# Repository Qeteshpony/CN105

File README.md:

# Mitsubishi CN105 compatible heatpump controller for ESPHome and Home Assistant

[Hardware Documentation](https://qeteshpony.github.io/CN105)

## Hardware fabrication

I ordered these boards from JLCPCB (Not a sponsor) and had only the smd components on the top side assembled. You then still need an ESP32-C6-WROOM-1 module (gets soldered on the bottom) and a Gaptec LME78_03-1.0 DC/DC Regulator. Also some header pins and a cable with a JST PAP-V-S PA 2.0 5 pin connector which goes into the CN105 port on the heatpumps main board. 

### Some details about the hardware

I decided to use the DC/DC regulator and pull power from the 12V pin of the heatpump since the 5V pin can't handle much current and I didn't want to risk damaging the heatpump. The 5V pin is just used for the pullups on the logic level converter since the heatpumps CN105 connector uses 5V logic which the ESP can't handle properly. 

LEDs 1 and 2 are connected to GPIO 23 and 22 and can be used freely by your software. 

LEDs 3 and 4 show activity on TX and RX and can be left out if you don't want the module to blink all the time... 

## Software

Mine are running with ESPHome and the external component found at [github.com/echavet/MitsubishiCN105ESPHome](https://github.com/echavet/MitsubishiCN105ESPHome)

Since this board uses the ESP32-C6, it can use WiFi as well as Thread to communicate with Home Assistant. 

Keep in mind that cheap serial adapters might not deliver enough power to successfully flash the ESP. I had to feed external power while flashing it. In that case only connect GND, RX and TX of the UART0 header to your serial adapter and feed anything between 6 and 36 volts (That's what the LME78 can handle) into the 12V pin of the boards CN105 header. 
When using ESPHome this is also just needed once. Updates can then be installed OTA.

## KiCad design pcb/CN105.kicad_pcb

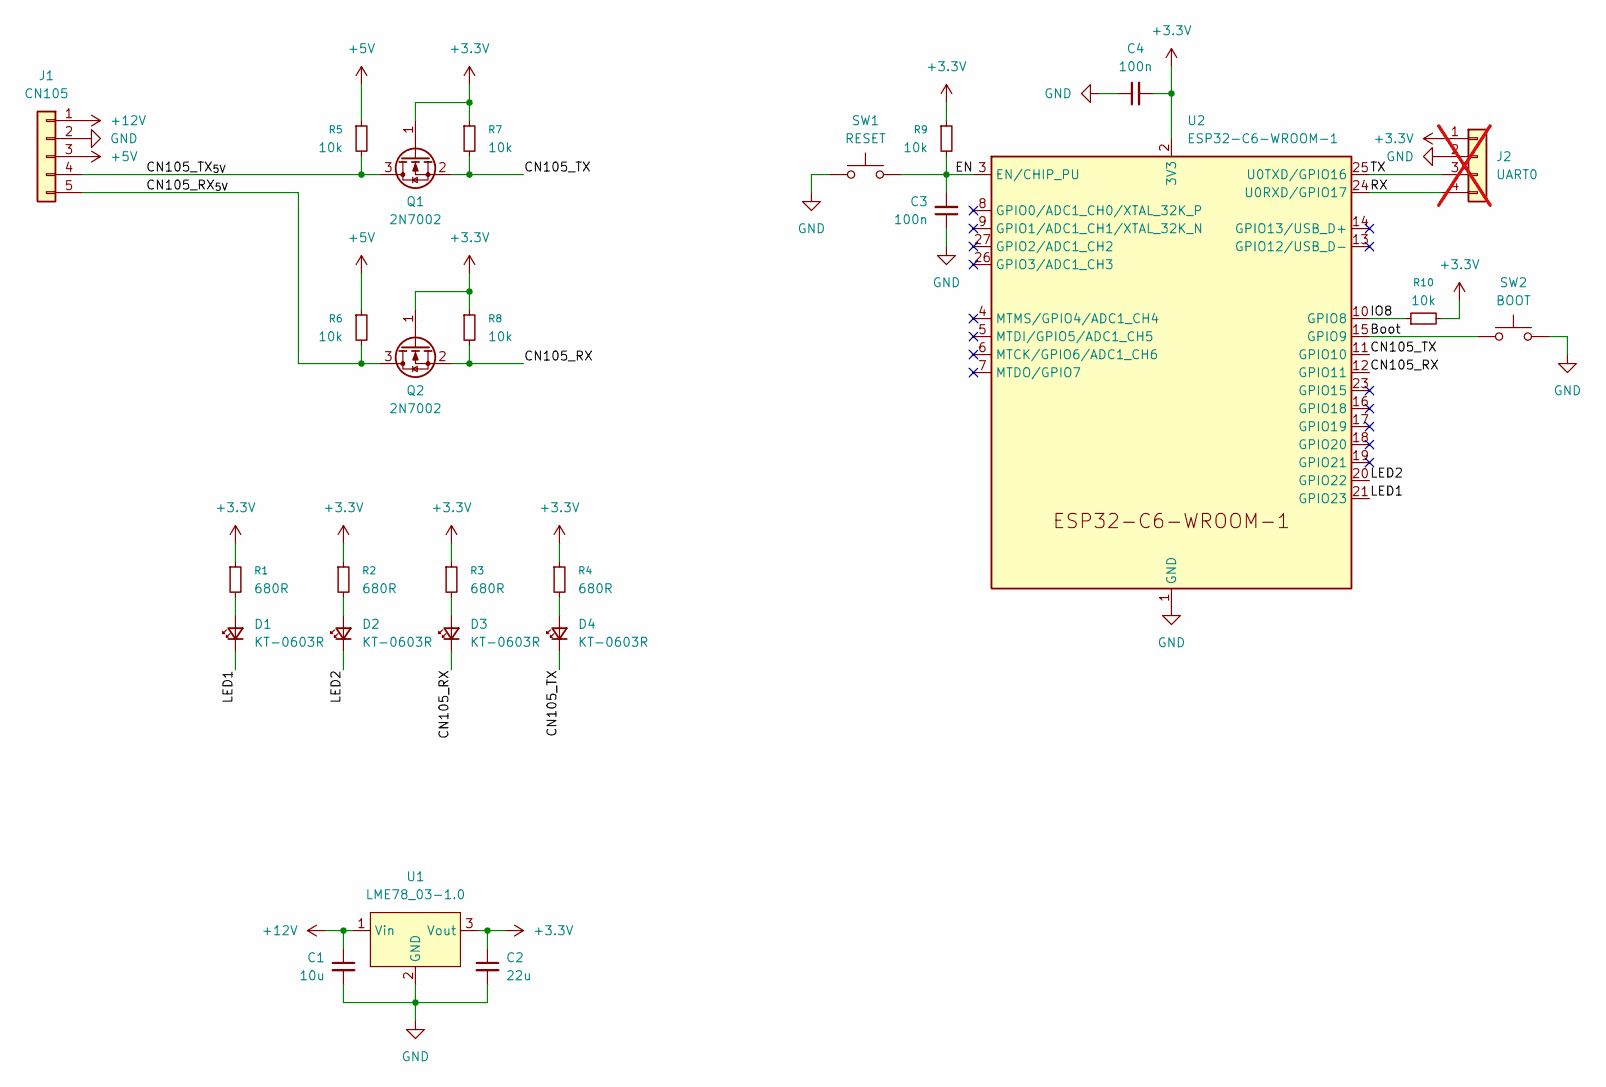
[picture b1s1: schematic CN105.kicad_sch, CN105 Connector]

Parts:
C1: 10u; C_0805_2012Metric; LCSC C440198
C2: 22u; C_0805_2012Metric; LCSC C45783
C3, C4: 100n; C_0402_1005Metric; LCSC C1525
D1, D2, D3, D4: KT-0603R; LED_0603_1608Metric; LCSC C2286
J1: CN105; PinHeader_1x05_P2.54mm_Horizontal
J2: UART0; PinHeader_2x02_P2.54mm_Vertical; not fitted
Q1, Q2: 2N7002; SOT-23; LCSC C8545
R1, R2, R3, R4: 680R; R_0402_1005Metric; LCSC C25130
R5, R6, R7, R8, R9, R10: 10k; R_0402_1005Metric; LCSC C25744
SW1: RESET; SW_Push_SPST_NO_Alps_SKRK; LCSC C720477
SW2: BOOT; SW_Push_SPST_NO_Alps_SKRK; LCSC C720477
U1: LME78_03-1.0; LME78_1.0-Series
U2: ESP32-C6-WROOM-1

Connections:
+3.3V: C2.1, C4.2, J2.1, Q1.1 (G), Q2.1 (G), R1.1, R2.1, R3.1, R4.1, R7.1, R8.1, R9.1, R10.2, U1.3 (Vout), U2.2 (3V3)
+5V: J1.3, R5.1, R6.1
+12V: C1.1, J1.1, U1.1 (Vin)
/Boot: SW2.1, U2.15 (GPIO9)
/CN105_RX: D3.1 (K), Q2.2 (S), R8.2, U2.12 (GPIO11)
/CN105_RX_{5V}: J1.5, Q2.3 (D), R6.2
/CN105_TX: D4.1 (K), Q1.2 (S), R7.2, U2.11 (GPIO10)
/CN105_TX_{5V}: J1.4, Q1.3 (D), R5.2
/EN: C3.2, R9.2, SW1.2, U2.3 (EN/CHIP_PU)
/IO8: R10.1, U2.10 (GPIO8)
/LED1: D1.1 (K), U2.21 (GPIO23)
/LED2: D2.1 (K), U2.20 (GPIO22)
/RX: J2.4, U2.24 (U0RXD/GPIO17)
/TX: J2.3, U2.25 (U0TXD/GPIO16)
GND: C1.2, C2.2, C3.1, C4.1, J1.2, J2.2, SW1.1, SW2.2, U1.2 (GND), U2.1 (GND), U2.28 (GND), U2.29 (GND)
unnamed: D1.2 (A), R1.2
unnamed: D2.2 (A), R2.2
unnamed: D3.2 (A), R3.2
unnamed: D4.2 (A), R4.2

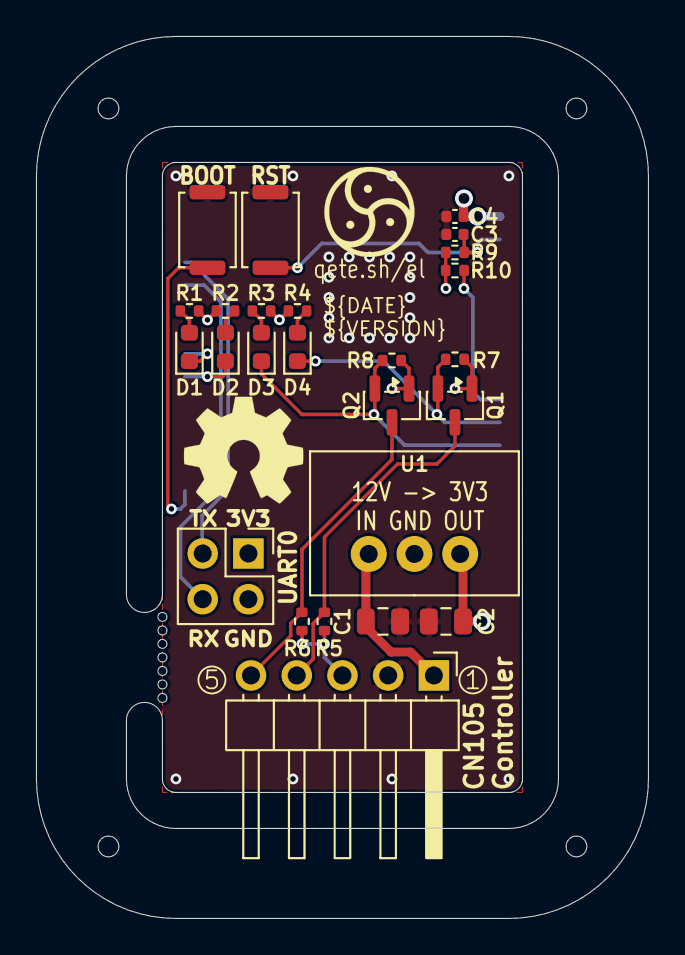
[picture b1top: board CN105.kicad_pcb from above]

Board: 4 copper layers, 34.0 x 49.0 mm, 27 parts (1 on the bottom side), 19 nets.

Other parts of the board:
mouse-bite-2mm-slot: VAL**; mouse-bite-2x5mm-slot-onesided-v2

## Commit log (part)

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2026-06-28 feat: initial commit
2026-06-28 chore(main): release 1.0.0
2026-06-28 docs: hardware and software description
2026-06-28 docs: fix typo
2026-06-28 ci: switch to main branch of reusable workflows
